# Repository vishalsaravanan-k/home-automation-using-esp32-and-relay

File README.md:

# 🏠 Home Automation using ESP32 with relay

This project is a basic **home automation system** built using an **ESP32**, capable of turning appliances **ON/OFF** through both **mobile app (via Wi-Fi)** and an **IR remote**. It is designed for beginners in IoT and embedded systems who want to automate devices like lights, fans, or other home appliances.

---

## 📦 Features
- ✅ Control appliances via **Wi-Fi** (mobile app/web interface)
- ✅ Support for **IR remote control** using TSOP1838 sensor
- ✅ 8-channel relay circuit for switching multiple devices
- ✅ Designed using **KiCad** and built around **ESP32-WROOM-32**
- ✅ USB-C interface with ESD protection and CH340 serial converter
- ✅ Power supply using AMS1117-3.3

---

## 🧰 Hardware Components
- ESP32-WROOM-32
- CH340C (USB to serial)
- 8 x Relays (5V)
- 8 x BC547 Transistors
- Diodes (1N4007), LEDs, Resistors
- TSOP1838 IR Receiver
- USB-C Connector
- AMS1117-3.3 Voltage Regulator

---

## 🚀 How It Works
1. ESP32 receives **IR commands** from a remote via TSOP1838.
2. Or, it receives **commands over Wi-Fi** from a mobile/web app.
3. Based on the command, the ESP32 toggles one of the 8 relay channels.
4. Each relay can be connected to an AC appliance to turn it ON or OFF.

---

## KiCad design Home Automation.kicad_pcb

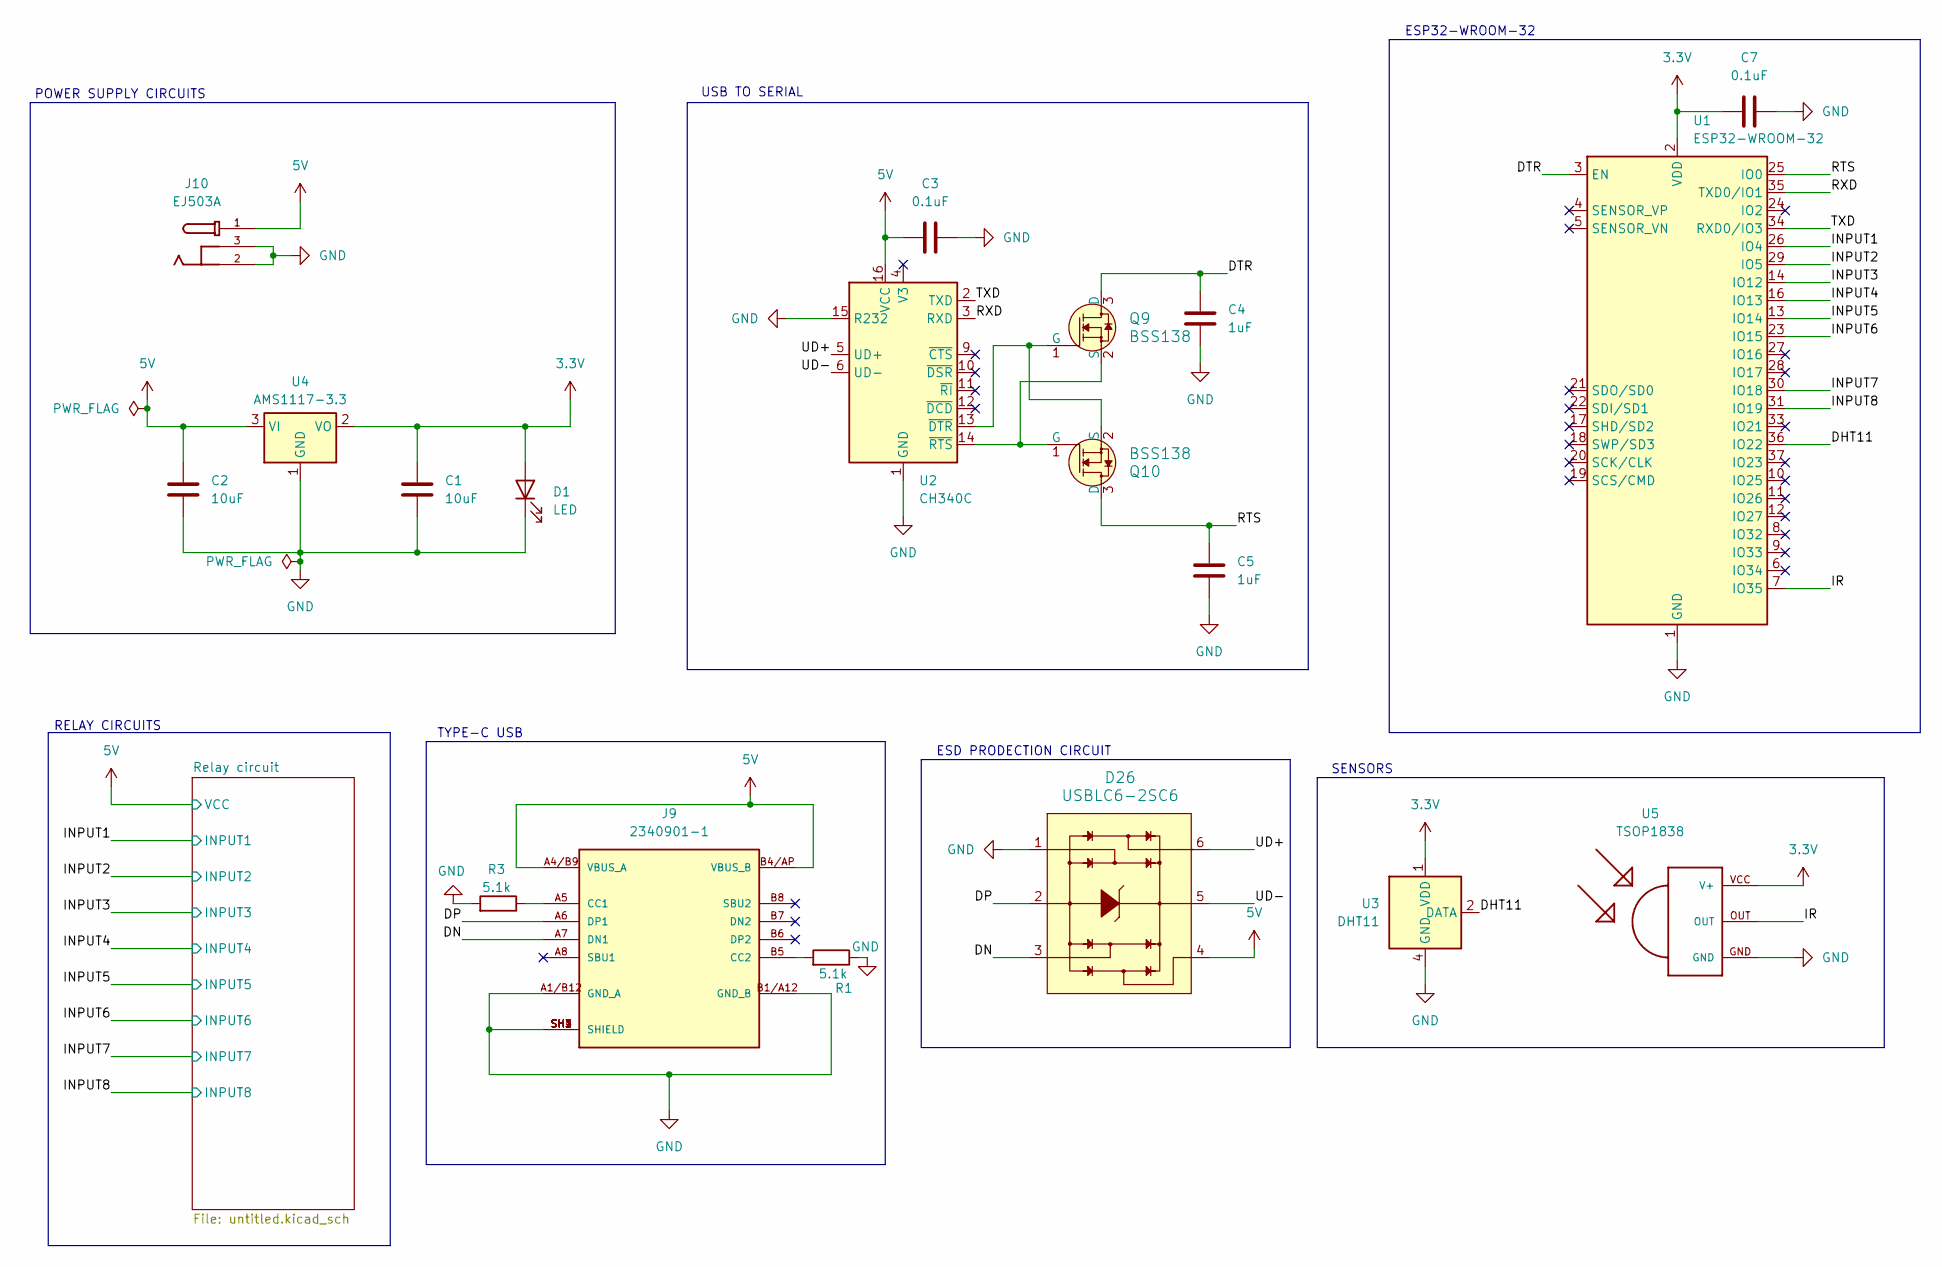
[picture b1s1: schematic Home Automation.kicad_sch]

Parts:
C1, C2: 10uF; C_1206_3216Metric_Pad1.33x1.80mm_HandSolder
C3, C7: 0.1uF; C_1206_3216Metric_Pad1.33x1.80mm_HandSolder
C4, C5: 1uF; C_1206_3216Metric_Pad1.33x1.80mm_HandSolder
D1: LED; LED_1812_4532Metric_Pad1.30x3.40mm_HandSolder
D26: USBLC6-2SC6; SOT95P280X145-6N; MPN USBLC6-2SC6; Digi-Key_PN 497-5235-1-ND
J9: 2340901-1; TE_2340901-1; PARTREV A
J10: EJ503A; MPD_EJ503A; PARTREV B
Q9, Q10: BSS138; SOT-23-3; MPN BSS138; Digi-Key_PN BSS138CT-ND
R1, R3: 5.1k; R_0805_2012Metric_Pad1.20x1.40mm_HandSolder
U1: ESP32-WROOM-32
U2: CH340C; SOIC-16_3.9x9.9mm_P1.27mm
U3: DHT11; Aosong_DHT11_5.5x12.0_P2.54mm
U4: AMS1117-3.3; SOT-223-3_TabPin2
U5: TSOP1838; TSOP18XX

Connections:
3.3V: C1.1, C7.1, D1.2 (A), U1.2 (VDD), U3.1 (VDD), U4.2 (VO), U5.VCC (V+)
5V: C2.1, C3.1, D26.4, J9.A4/B9 (VBUS_A), J9.B4/AP (VBUS_B), J10.1, U2.16 (VCC), U4.3 (VI); also elsewhere on the board
/DHT11: U1.36 (IO22), U3.2 (DATA)
/DN: D26.3, J9.A7 (DN1)
/DP: D26.2, J9.A6 (DP1)
/DTR: C4.2, Q9.3 (D), U1.3 (EN)
/INPUT1: U1.26 (IO4); also elsewhere on the board
/INPUT2: U1.29 (IO5); also elsewhere on the board
/INPUT3: U1.14 (IO12); also elsewhere on the board
/INPUT4: U1.16 (IO13); also elsewhere on the board
/INPUT5: U1.13 (IO14); also elsewhere on the board
/INPUT6: U1.23 (IO15); also elsewhere on the board
/INPUT7: U1.30 (IO18); also elsewhere on the board
/INPUT8: U1.31 (IO19); also elsewhere on the board
/IR: U1.7 (IO35), U5.OUT
/RTS: C5.2, Q10.3 (D), U1.25 (IO0)
/RXD: U1.35 (TXD0/IO1), U2.3 (RXD)
/TXD: U1.34 (RXD0/IO3), U2.2 (TXD)
/UD+: D26.6, U2.5 (UD+)
/UD-: D26.5, U2.6 (UD-)
GND: C1.2, C2.2, C3.2, C4.1, C5.1, C7.2, D1.1 (K), D26.1, J9.A1/B12 (GND_A), J9.B1/A12 (GND_B), J9.SH1 (SHIELD), J9.SH2 (SHIELD), J9.SH3 (SHIELD), J9.SH4 (SHIELD), J10.2, J10.3, R1.1, R3.2, U1.1 (GND), U1.15 (GND), U1.38 (GND), U1.39 (GND), U2.1 (GND), U2.15 (R232), U3.4 (GND), U4.1 (GND), U5.GND; also elsewhere on the board
unnamed: J9.A5 (CC1), R3.1
unnamed: J9.B5 (CC2), R1.2
unnamed: Q9.2 (S), Q10.1 (G), U2.14 (~RTS)
unnamed: Q9.1 (G), Q10.2 (S), U2.13 (~DTR)

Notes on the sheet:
SENSORS
ESD PRODECTION CIRCUIT
USB TO SERIAL
ESP32-WROOM-32
POWER SUPPLY CIRCUITS
TYPE-C USB
RELAY CIRCUITS

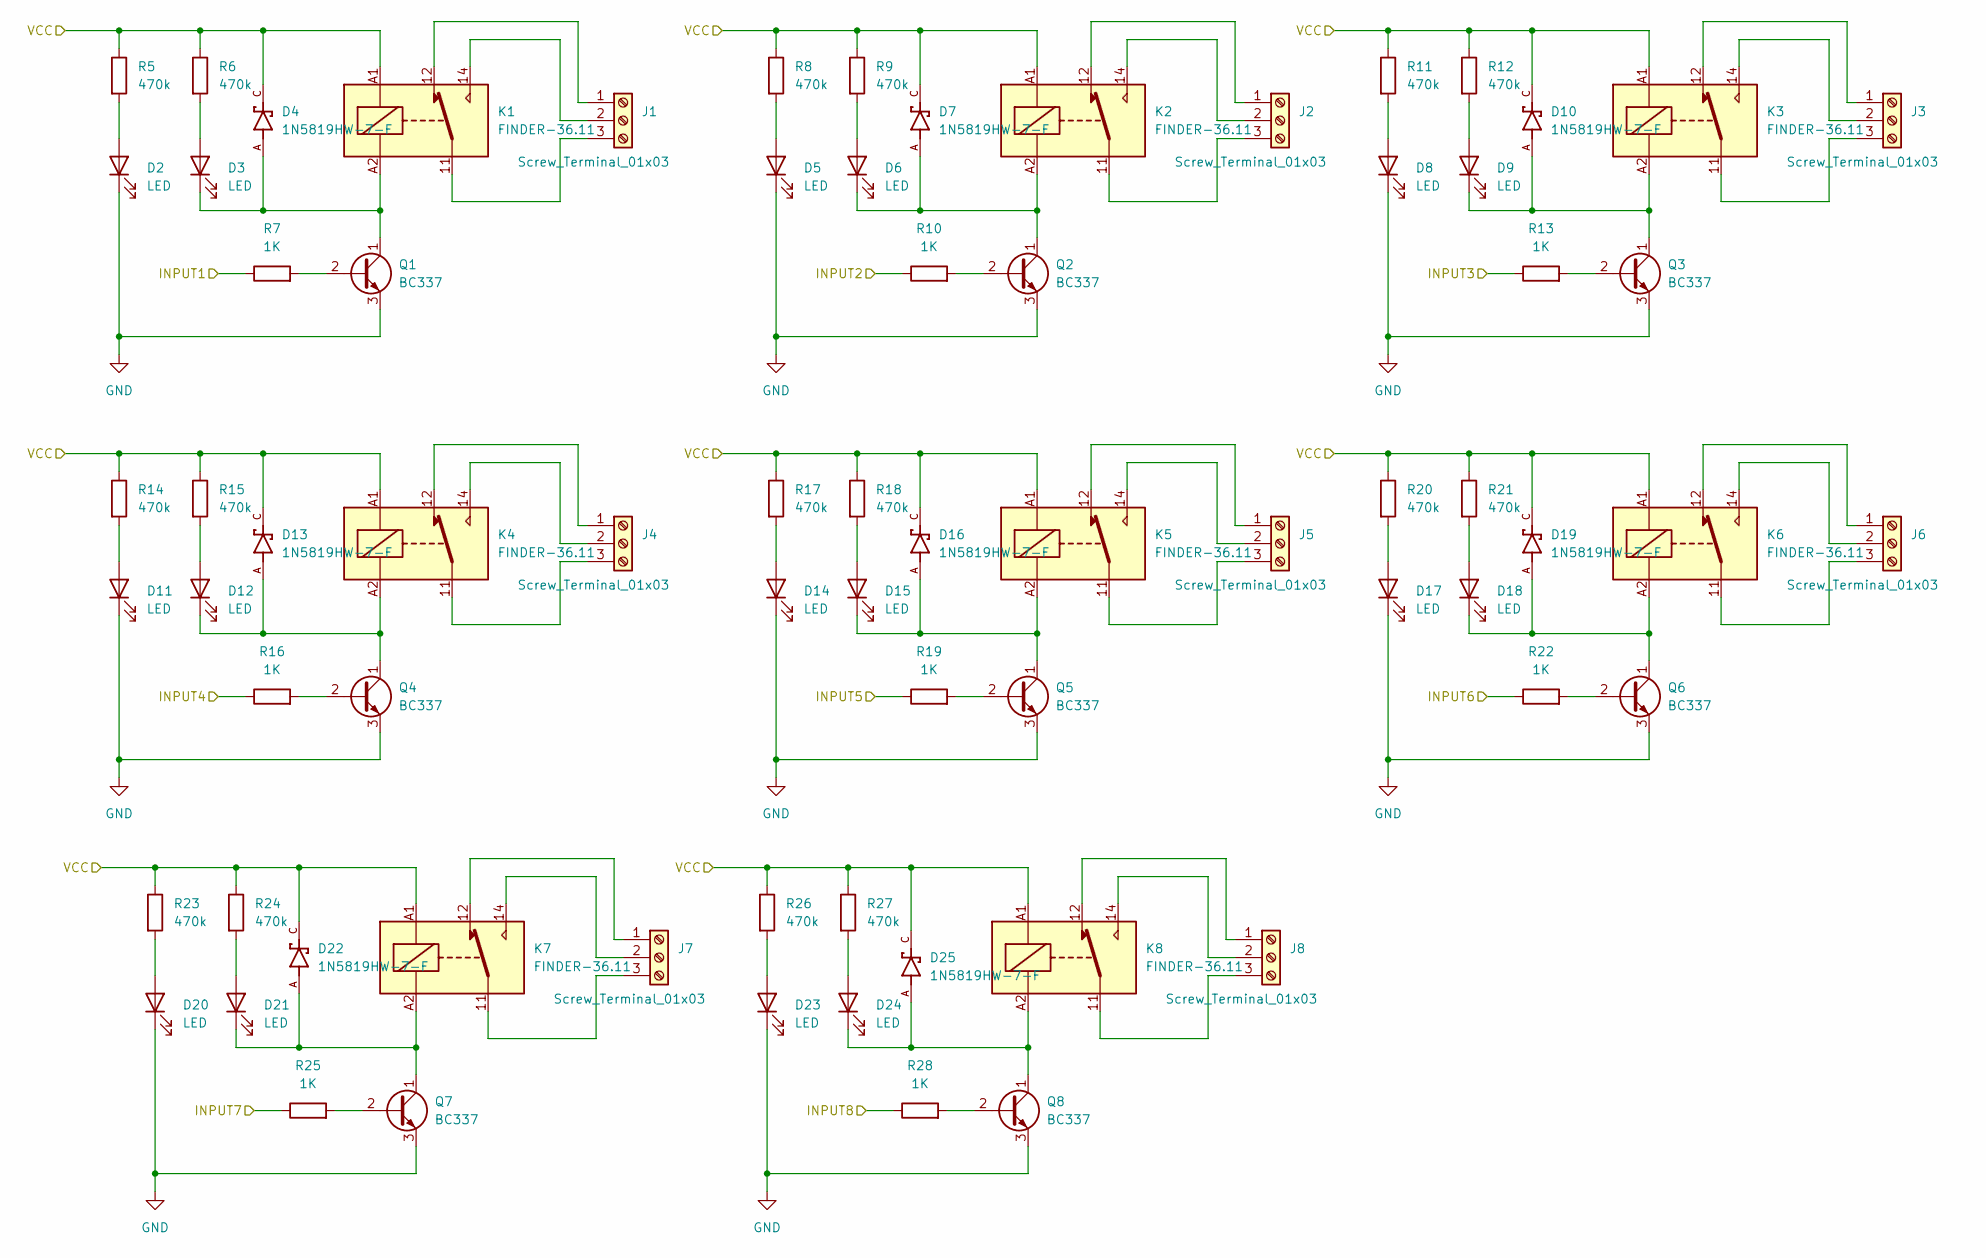
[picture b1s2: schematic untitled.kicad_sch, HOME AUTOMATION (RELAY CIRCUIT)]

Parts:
D2, D3, D5, D6, D8, D9, D11, D12, D14, D15, D17, D18, D20, D21, D23, D24: LED; LED_1812_4532Metric_Pad1.30x3.40mm_HandSolder
D4, D7, D10, D13, D16, D19, D22, D25: 1N5819HW-7-F; SOD3715X145N; PARTREV 18-2
J1, J2, J3, J4, J5, J6, J7, J8: Screw_Terminal_01x03; CUI_TB004-508-03BE
K1, K2, K3, K4, K5, K6, K7, K8: FINDER-36.11; Relay_SPDT_Finder_36.11
Q1, Q2, Q3, Q4, Q5, Q6, Q7, Q8: BC337; SOT-23-3
R5, R6, R8, R9, R11, R12, R14, R15, R17, R18, R20, R21, R23, R24, R26, R27: 470k; R_0805_2012Metric_Pad1.20x1.40mm_HandSolder
R7, R10, R13, R16, R19, R22, R25, R28: 1K; R_0805_2012Metric_Pad1.20x1.40mm_HandSolder

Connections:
5V: D4.C, D7.C, D10.C, D13.C, D16.C, D19.C, D22.C, D25.C, K1.A1, K2.A1, K3.A1, K4.A1, K5.A1, K6.A1, K7.A1, K8.A1, R5.1, R6.1, R8.1, R9.1, R11.1, R12.1, R14.1, R15.1, R17.1, R18.1, R20.1, R21.1, R23.1, R24.1, R26.1, R27.1; also elsewhere on the board
/INPUT1: R7.1; also elsewhere on the board
/INPUT2: R10.1; also elsewhere on the board
/INPUT3: R13.1; also elsewhere on the board
/INPUT4: R16.1; also elsewhere on the board
/INPUT5: R19.1; also elsewhere on the board
/INPUT6: R22.1; also elsewhere on the board
/INPUT7: R25.1; also elsewhere on the board
/INPUT8: R28.1; also elsewhere on the board
GND: D2.1 (K), D5.1 (K), D8.1 (K), D11.1 (K), D14.1 (K), D17.1 (K), D20.1 (K), D23.1 (K), Q1.3 (E), Q2.3 (E), Q3.3 (E), Q4.3 (E), Q5.3 (E), Q6.3 (E), Q7.3 (E), Q8.3 (E); also elsewhere on the board
unnamed: D2.2 (A), R5.2
unnamed: D3.2 (A), R6.2
unnamed: D3.1 (K), D4.A, K1.A2, Q1.1 (C)
unnamed: D5.2 (A), R8.2
unnamed: D6.2 (A), R9.2
unnamed: D6.1 (K), D7.A, K2.A2, Q2.1 (C)
unnamed: D8.2 (A), R11.2
unnamed: D9.2 (A), R12.2
unnamed: D9.1 (K), D10.A, K3.A2, Q3.1 (C)
unnamed: D11.2 (A), R14.2
unnamed: D12.2 (A), R15.2
unnamed: D12.1 (K), D13.A, K4.A2, Q4.1 (C)
unnamed: D14.2 (A), R17.2
unnamed: D15.2 (A), R18.2
unnamed: D15.1 (K), D16.A, K5.A2, Q5.1 (C)
unnamed: D17.2 (A), R20.2
unnamed: D18.2 (A), R21.2
unnamed: D18.1 (K), D19.A, K6.A2, Q6.1 (C)
unnamed: D20.2 (A), R23.2
unnamed: D21.2 (A), R24.2
unnamed: D21.1 (K), D22.A, K7.A2, Q7.1 (C)
unnamed: D23.2 (A), R26.2
unnamed: D24.2 (A), R27.2
unnamed: D24.1 (K), D25.A, K8.A2, Q8.1 (C)
unnamed: J1.1, K1.12
unnamed: J1.2, K1.14
unnamed: J1.3, K1.11
unnamed: J2.1, K2.12
unnamed: J2.2, K2.14
unnamed: J2.3, K2.11
unnamed: J3.1, K3.12
unnamed: J3.2, K3.14
unnamed: J3.3, K3.11
unnamed: J4.1, K4.12
unnamed: J4.2, K4.14
unnamed: J4.3, K4.11
unnamed: J5.1, K5.12
unnamed: J5.2, K5.14
unnamed: J5.3, K5.11
unnamed: J6.1, K6.12
unnamed: J6.2, K6.14
unnamed: J6.3, K6.11
unnamed: J7.1, K7.12
unnamed: J7.2, K7.14
unnamed: J7.3, K7.11
unnamed: J8.1, K8.12
unnamed: J8.2, K8.14
unnamed: J8.3, K8.11
unnamed: Q1.2 (B), R7.2
unnamed: Q2.2 (B), R10.2
unnamed: Q3.2 (B), R13.2
unnamed: Q4.2 (B), R16.2
unnamed: Q5.2 (B), R19.2
unnamed: Q6.2 (B), R22.2
unnamed: Q7.2 (B), R25.2
unnamed: Q8.2 (B), R28.2

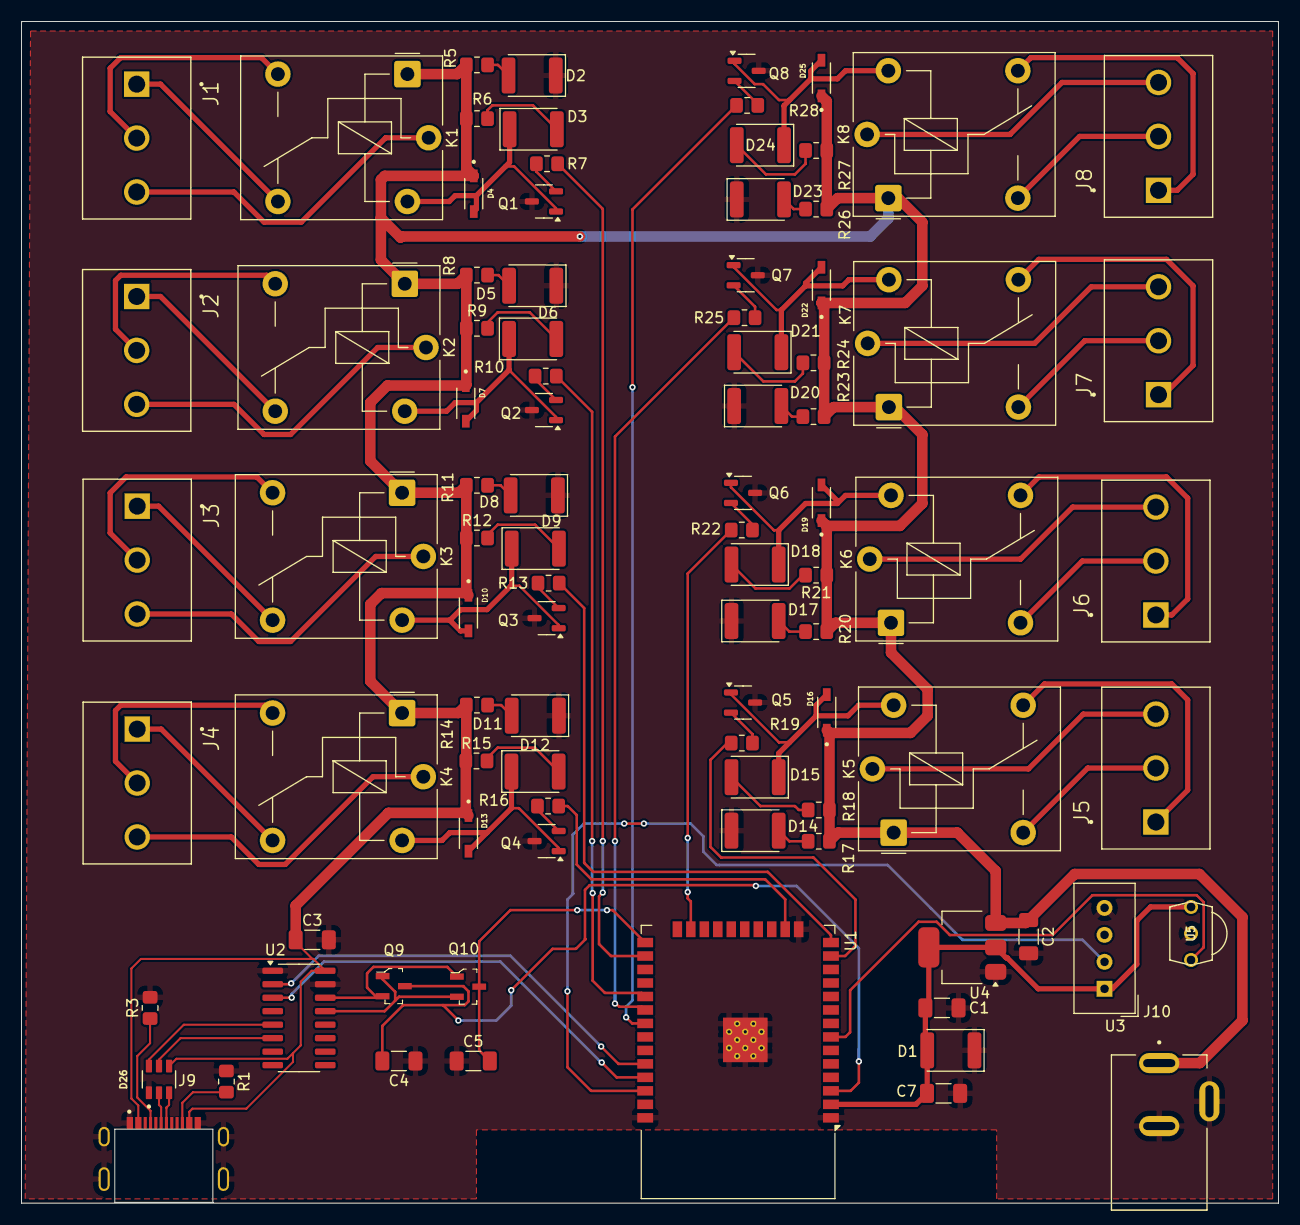
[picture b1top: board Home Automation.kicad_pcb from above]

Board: 2 copper layers, 118.4 x 111.3 mm, 91 parts (0 on the bottom side), 81 nets.

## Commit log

2025-06-08 Initial commit - Home Automation ESP32 Project
2025-06-08 Image uploaded
